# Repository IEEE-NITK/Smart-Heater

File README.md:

# Smart-Heater
A novel device to link with a water heater to control the temprature of water and keep it between certain desirable levels.

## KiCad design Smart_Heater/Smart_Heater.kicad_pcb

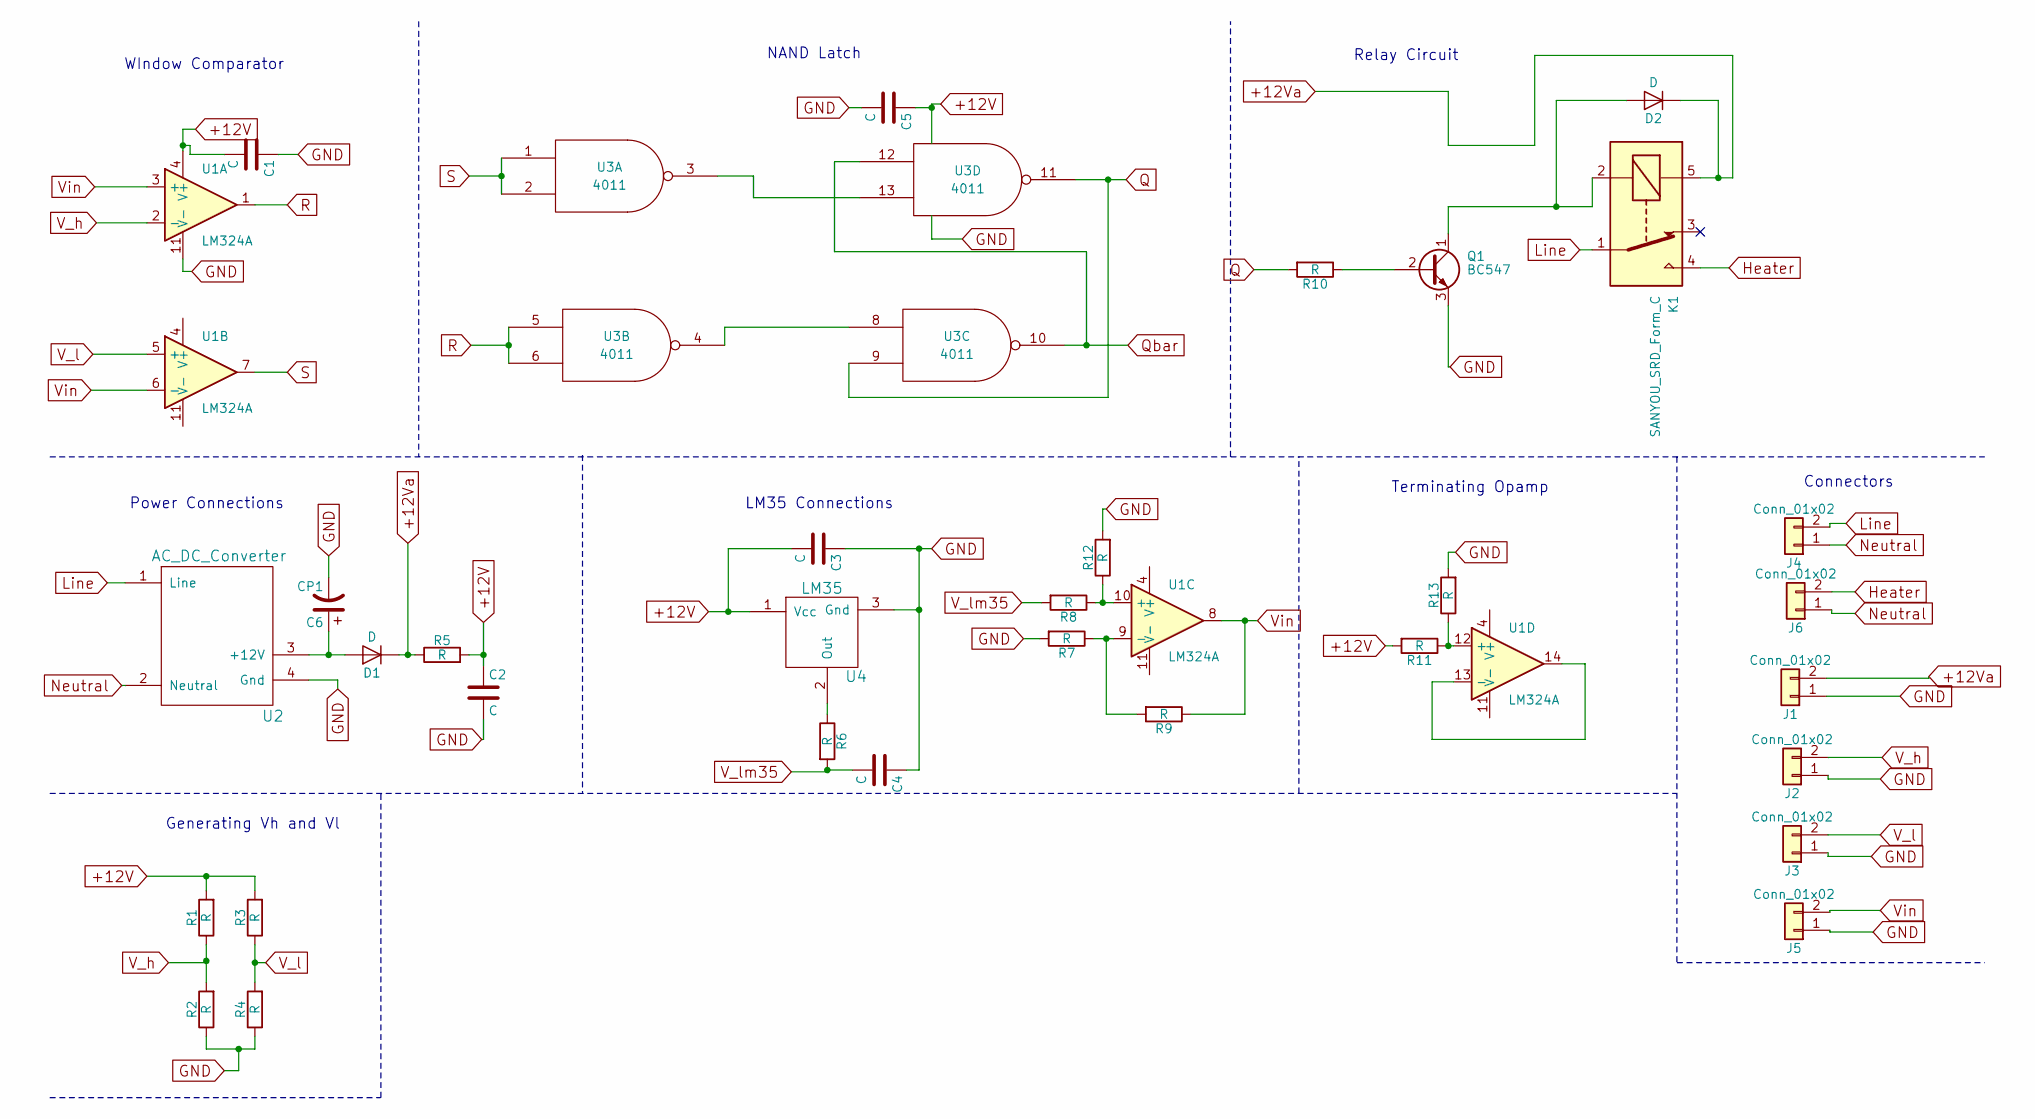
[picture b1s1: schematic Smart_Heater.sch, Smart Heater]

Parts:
C1, C2, C3, C4, C5: C; C_Disc_D9.0mm_W2.5mm_P5.00mm
C6: CP1; CP_Radial_D8.0mm_P3.50mm
D1, D2: D; D_DO-41_SOD81_P10.16mm_Horizontal
J1, J2, J3, J5: Conn_01x02; Pin_Header_Straight_1x02_Pitch2.54mm
J4, J6: Conn_01x02; TerminalBlock_Philmore_TB132_02x5mm_Straight
K1: SANYOU_SRD_Form_C; Relay_SPDT_SANYOU_SRD_Series_Form_C
Q1: BC547; TO-92_Molded_Narrow
R1, R2, R3, R4, R5, R6, R7, R8, R9, R10, R11, R12, R13: R; R_Axial_DIN0207_L6.3mm_D2.5mm_P10.16mm_Horizontal
U1: LM324A; DIP-14_W7.62mm_LongPads
U2: AC_DC_Converter; Combicon_Connector
U3: 4011; DIP-14_W7.62mm_LongPads
U4: LM35; Pin_Header_Straight_1x03_Pitch2.54mm

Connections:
+12V: C1.2, C2.1, C3.2, C5.1, R1.2, R3.2, R5.2, R11.2, U1.4 (V+), U3.14 (VDD), U4.1 (Vcc)
+12Va: D1.1 (K), D2.1 (K), J1.2, K1.5, R5.1
GND: C1.1, C2.2, C3.1, C4.1, C5.2, C6.2, J1.1, J2.1, J3.1, J5.1, Q1.3 (E), R2.1, R4.1, R7.2, R12.2, R13.2, U1.11 (V-), U2.4 (Gnd), U3.7 (VSS), U4.3 (Gnd)
Heater: J6.2, K1.4
Line: J4.2, K1.1, U2.1 (Line)
unnamed: C6.1, D1.2 (A), U2.3 (+12V)
unnamed: D2.2 (A), K1.2, Q1.1 (C)
unnamed: Q1.2 (B), R10.1
unnamed: R6.1, U4.2 (Out)
unnamed: R7.1, R9.2, U1.9 (-)
unnamed: R11.1, R13.1, U1.12 (+)
unnamed: R8.1, R12.1, U1.10 (+)
unnamed: U1.13 (-), U1.14
unnamed: U3.4, U3.8
unnamed: U3.3, U3.13
Neutral: J4.1, J6.1, U2.2 (Neutral)
Q: R10.2, U3.9, U3.11
Qbar: U3.10, U3.12
R: U1.1, U3.5, U3.6
S: U1.7, U3.1, U3.2
V_h: J2.2, R1.1, R2.2, U1.2 (-)
V_l: J3.2, R3.1, R4.2, U1.5 (+)
V_lm35: C4.2, R6.2, R8.2
Vin: J5.2, R9.1, U1.3 (+), U1.6 (-), U1.8

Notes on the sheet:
WIndow Comparator
NAND Latch
Relay Circuit
LM35 Connections
Power Connections
Connectors
Terminating Opamp
Generating Vh and Vl

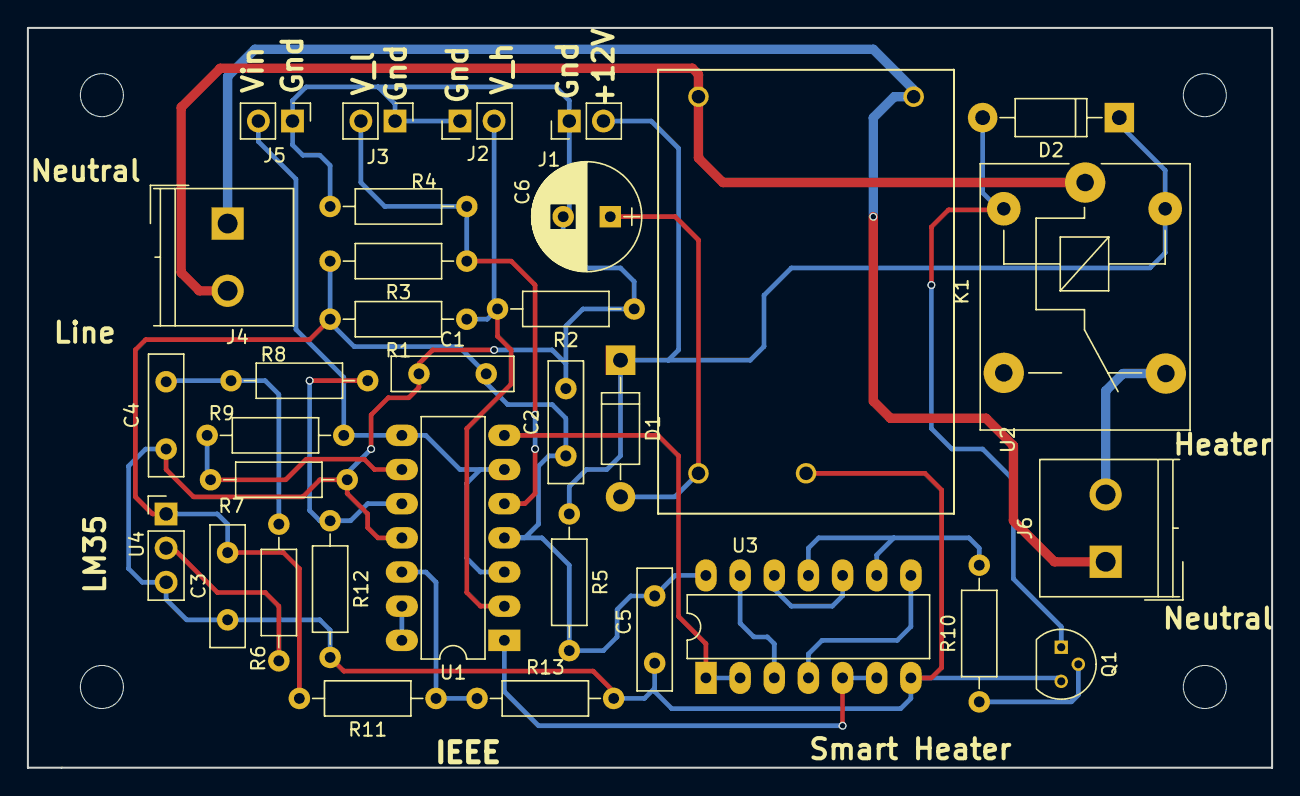
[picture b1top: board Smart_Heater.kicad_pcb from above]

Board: 2 copper layers, 92.5 x 55.0 mm, 33 parts (0 on the bottom side), 24 nets.
